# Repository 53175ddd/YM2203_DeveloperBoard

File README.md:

# YM2203_DeveloperBoard

YAMAHA 製 FM 音源 IC YM2203 用の SPI インターフェース開発ボード

# 部品表

| 部品番号 | 部品名 | 秋月リンク |
|:----|:----|:----:|
| C1 ~ C3 | 0.1uF | <https://akizukidenshi.com/catalog/g/g110147/> |
| C4 | 10uF | <https://akizukidenshi.com/catalog/g/g117897/> |
| C5, C6 | 47uF | <https://akizukidenshi.com/catalog/g/g110270/> |
| R1 ~ R10 | 10kΩ | <https://akizukidenshi.com/catalog/g/g125103/> |
| U1 | YM2203 | - |
| U2 | YM3014B | - |
| U3 | MCP23S17 | <https://akizukidenshi.com/catalog/g/g110644/> |
| U4, U5 | NJM4558DD | <https://akizukidenshi.com/catalog/g/g111236/> |
| U6 | 1MHz Osc | <https://akizukidenshi.com/catalog/g/g110385/> |

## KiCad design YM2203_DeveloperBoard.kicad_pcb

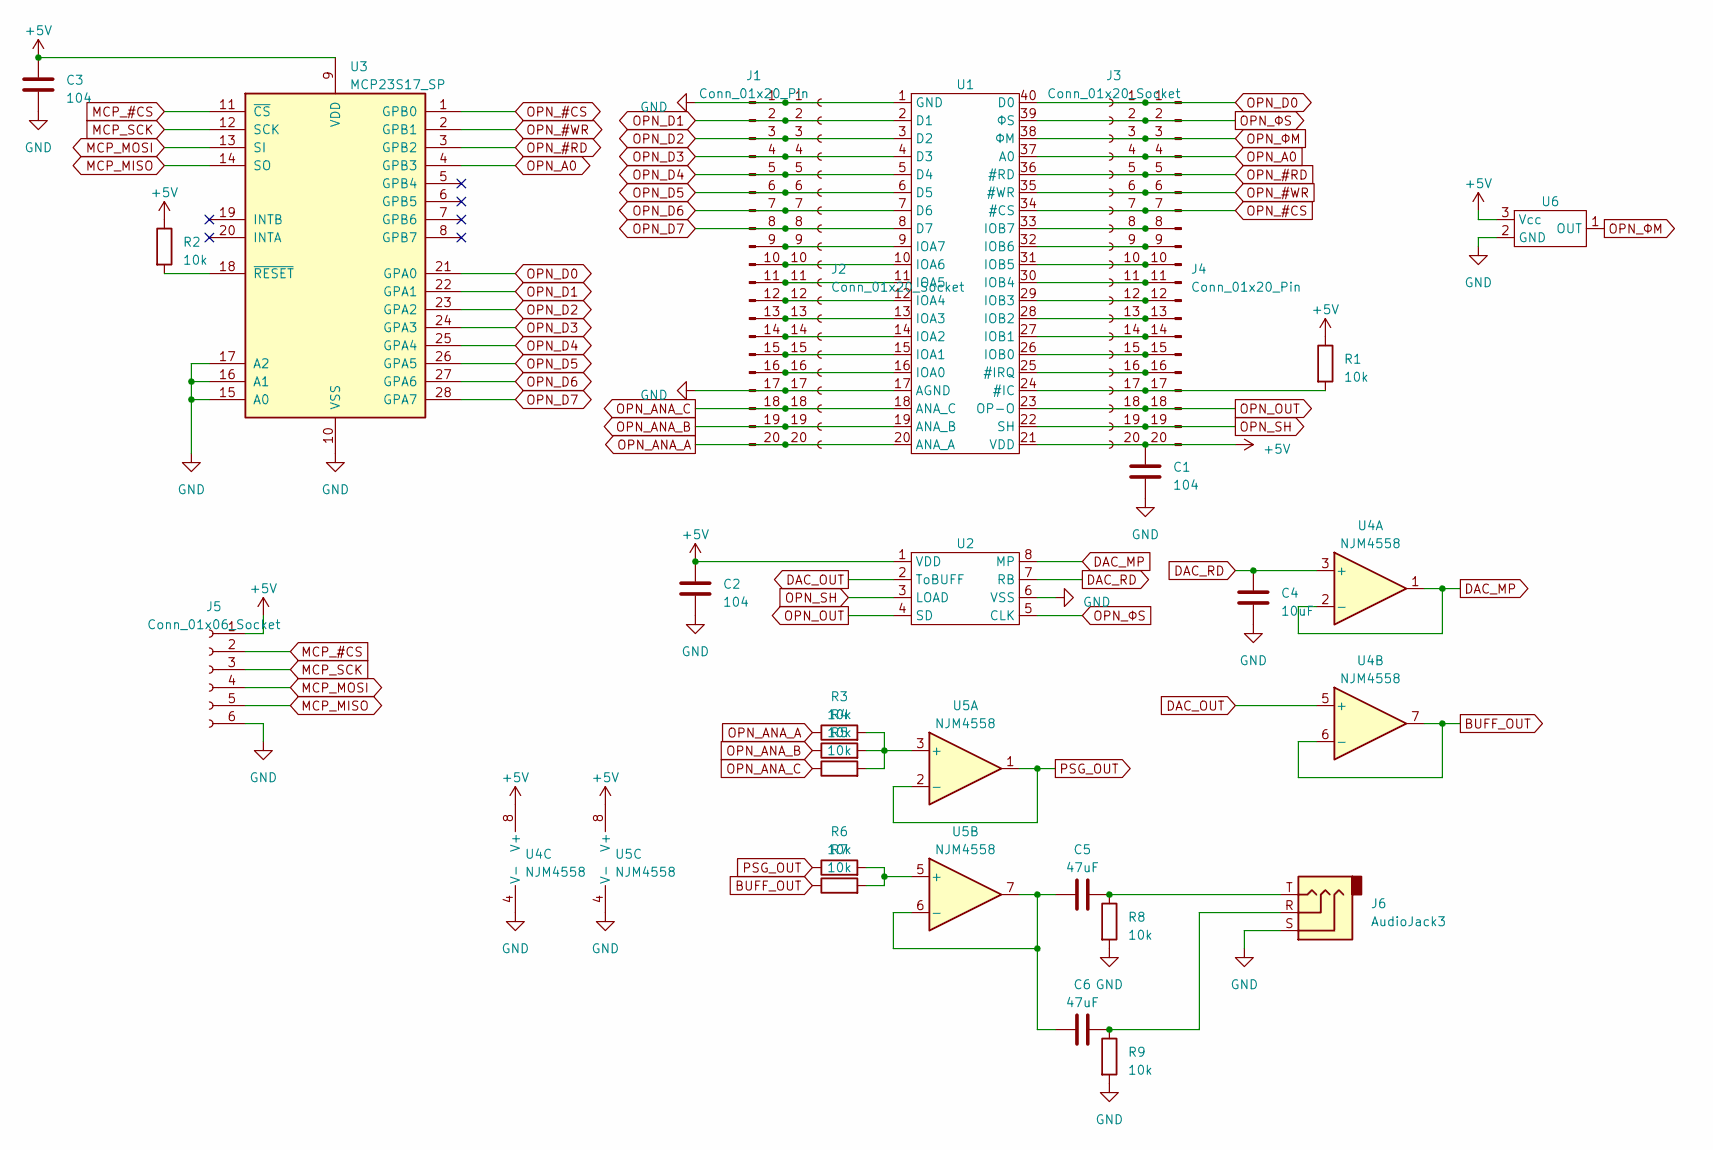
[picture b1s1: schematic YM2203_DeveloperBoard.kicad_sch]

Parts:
C1, C2, C3: 104; C_Disc_D5.0mm_W2.5mm_P5.00mm
C4: 10uF; CP_Radial_D6.3mm_P2.50mm
C5, C6: 47uF; CP_Radial_D6.3mm_P2.50mm
J1, J4: Conn_01x20_Pin; PinHeader_1x20_P2.54mm_Vertical
J2, J3: Conn_01x20_Socket; PinSocket_1x20_P2.54mm_Vertical
J5: Conn_01x06_Socket; PinSocket_1x06_P2.54mm_Vertical
J6: AudioJack3; Jack_3.5mm_Switronic_ST-005-G_horizontal
R1, R2, R3, R4, R5, R6, R7, R8, R9: 10k; R_Axial_DIN0207_L6.3mm_D2.5mm_P10.16mm_Horizontal
U1: DIP-40_W15.24mm_Socket
U2: DIP-8_W7.62mm_Socket
U3: MCP23S17_SP; DIP-28_W7.62mm
U4, U5: NJM4558; DIP-8_W7.62mm_Socket
U6: TO-92_Inline_Wide

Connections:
+5V: C1.1, C2.1, C3.1, J3.20, J4.20, J5.1, R1.1, R2.1, U1.21 (VDD), U2.1 (VDD), U3.9 (VDD), U4.8 (V+), U5.8 (V+), U6.3 (Vcc)
BUFF_OUT: R7.1, U4.6 (-), U4.7
DAC_MP: U2.8 (MP), U4.1, U4.2 (-)
DAC_OUT: U2.2 (ToBUFF), U4.5 (+)
DAC_RD: C4.1, U2.7 (RB), U4.3 (+)
GND: C1.2, C2.2, C3.2, C4.2, J1.1, J1.17, J2.1, J2.17, J5.6, J6.S, R8.2, R9.2, U1.1 (GND), U1.17 (AGND), U2.6 (VSS), U3.10 (VSS), U3.15 (A0), U3.16 (A1), U3.17 (A2), U4.4 (V-), U5.4 (V-), U6.2 (GND)
MCP_#CS: J5.2, U3.11 (~CS)
MCP_MISO: J5.5, U3.14 (SO)
MCP_MOSI: J5.4, U3.13 (SI)
MCP_SCK: J5.3, U3.12 (SCK)
unnamed: C5.2, J6.T, R8.1
unnamed: C6.2, J6.R, R9.1
unnamed: J1.9, J2.9, U1.9 (IOA7)
unnamed: J1.10, J2.10, U1.10 (IOA6)
unnamed: J1.11, J2.11, U1.11 (IOA5)
unnamed: J1.12, J2.12, U1.12 (IOA4)
unnamed: J1.13, J2.13, U1.13 (IOA3)
unnamed: J1.14, J2.14, U1.14 (IOA2)
unnamed: J1.15, J2.15, U1.15 (IOA1)
unnamed: J1.16, J2.16, U1.16 (IOA0)
unnamed: J3.8, J4.8, U1.33 (IOB7)
unnamed: J3.9, J4.9, U1.32 (IOB6)
unnamed: J3.10, J4.10, U1.31 (IOB5)
unnamed: J3.11, J4.11, U1.30 (IOB4)
unnamed: J3.12, J4.12, U1.29 (IOB3)
unnamed: J3.13, J4.13, U1.28 (IOB2)
unnamed: J3.14, J4.14, U1.27 (IOB1)
unnamed: J3.15, J4.15, U1.26 (IOB0)
unnamed: J3.16, J4.16, U1.25 (#IRQ)
unnamed: J3.17, J4.17, R1.2, U1.24 (#IC)
unnamed: R2.2, U3.18 (~RESET)
unnamed: R3.2, R4.2, R5.2, U5.3 (+)
unnamed: R6.2, R7.2, U5.5 (+)
unnamed: C5.1, C6.1, U5.6 (-), U5.7
OPN_#CS: J3.7, J4.7, U1.34 (#CS), U3.1 (GPB0)
OPN_#RD: J3.5, J4.5, U1.36 (#RD), U3.3 (GPB2)
OPN_#WR: J3.6, J4.6, U1.35 (#WR), U3.2 (GPB1)
OPN_A0: J3.4, J4.4, U1.37 (A0), U3.4 (GPB3)
OPN_ANA_A: J1.20, J2.20, R3.1, U1.20 (ANA_A)
OPN_ANA_B: J1.19, J2.19, R4.1, U1.19 (ANA_B)
OPN_ANA_C: J1.18, J2.18, R5.1, U1.18 (ANA_C)
OPN_D0: J3.1, J4.1, U1.40 (D0), U3.21 (GPA0)
OPN_D1: J1.2, J2.2, U1.2 (D1), U3.22 (GPA1)
OPN_D2: J1.3, J2.3, U1.3 (D2), U3.23 (GPA2)
OPN_D3: J1.4, J2.4, U1.4 (D3), U3.24 (GPA3)
OPN_D4: J1.5, J2.5, U1.5 (D4), U3.25 (GPA4)
OPN_D5: J1.6, J2.6, U1.6 (D5), U3.26 (GPA5)
OPN_D6: J1.7, J2.7, U1.7 (D6), U3.27 (GPA6)
OPN_D7: J1.8, J2.8, U1.8 (D7), U3.28 (GPA7)
OPN_OUT: J3.18, J4.18, U1.23 (OP-O), U2.4 (SD)
OPN_SH: J3.19, J4.19, U1.22 (SH), U2.3 (LOAD)
OPN_ΦM: J3.3, J4.3, U1.38 (ΦM), U6.1 (OUT)
OPN_ΦS: J3.2, J4.2, U1.39 (ΦS), U2.5 (CLK)
PSG_OUT: R6.1, U5.1, U5.2 (-)

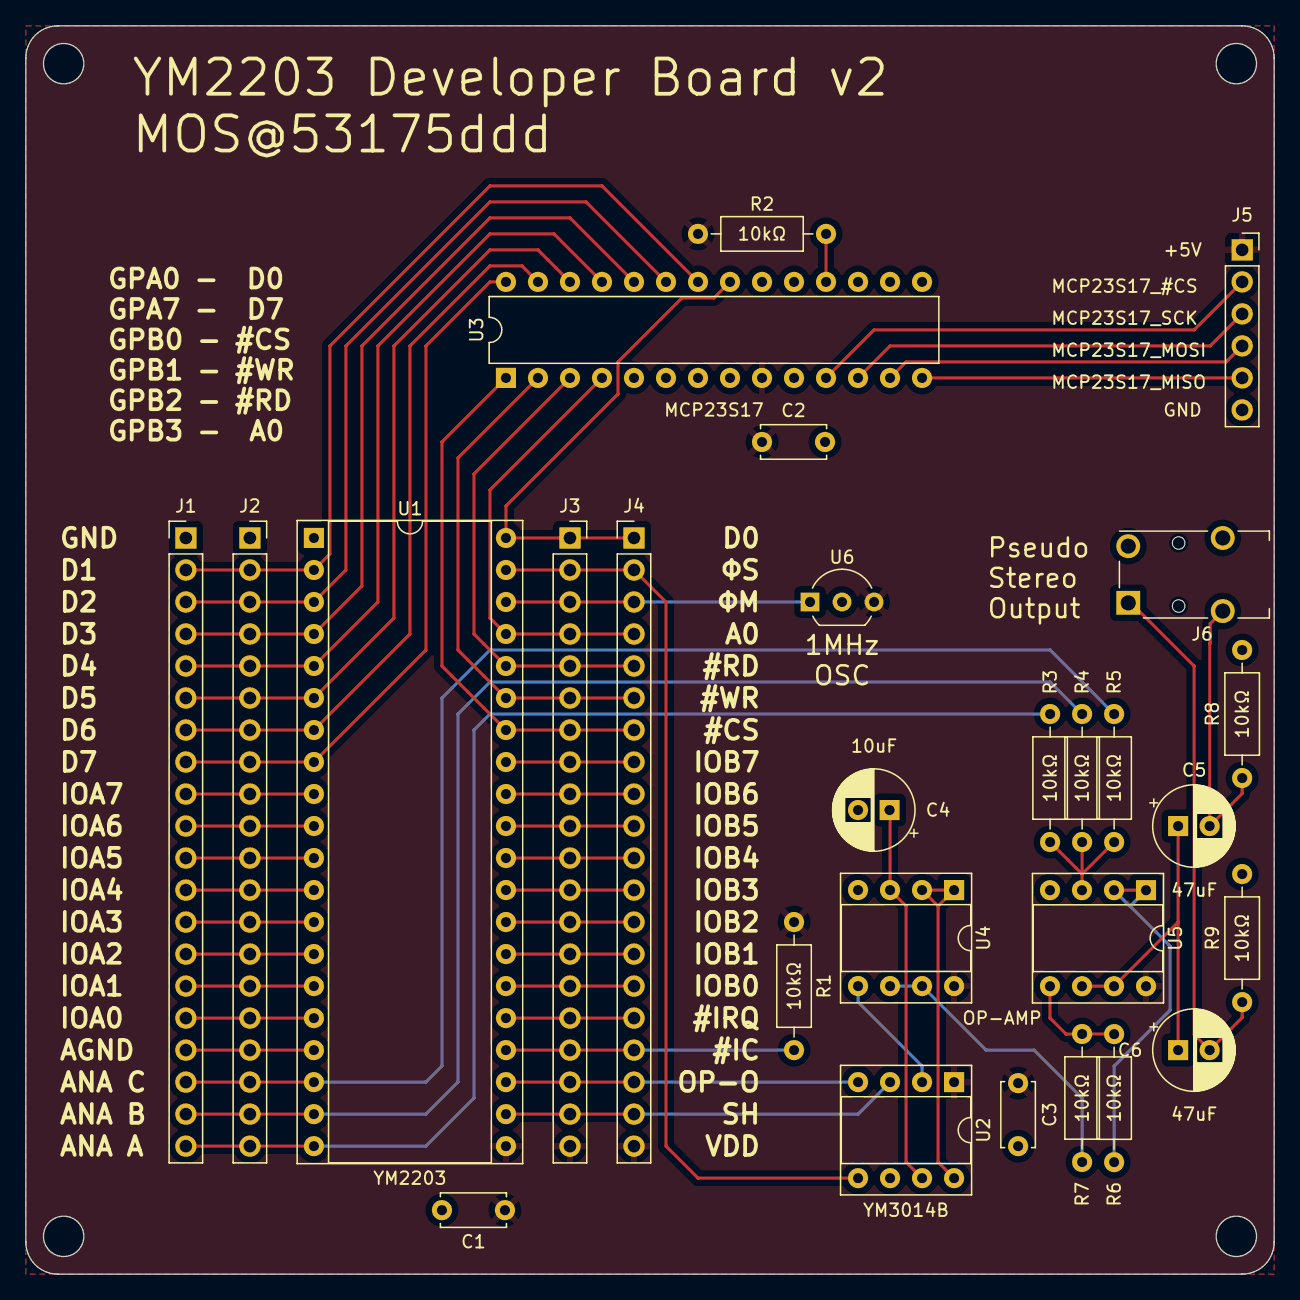
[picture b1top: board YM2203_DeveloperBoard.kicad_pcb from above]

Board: 2 copper layers, 99.1 x 99.1 mm, 27 parts (0 on the bottom side), 54 nets.

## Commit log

2024-01-18 add bom
2024-01-26 fix link
2024-02-05 U5 の電源未配線を修正
2024-02-06 基板整形，シルク印刷追記修正
2024-02-11 部品表更新
2024-02-24 update to v2
2024-03-28 タグを修正
